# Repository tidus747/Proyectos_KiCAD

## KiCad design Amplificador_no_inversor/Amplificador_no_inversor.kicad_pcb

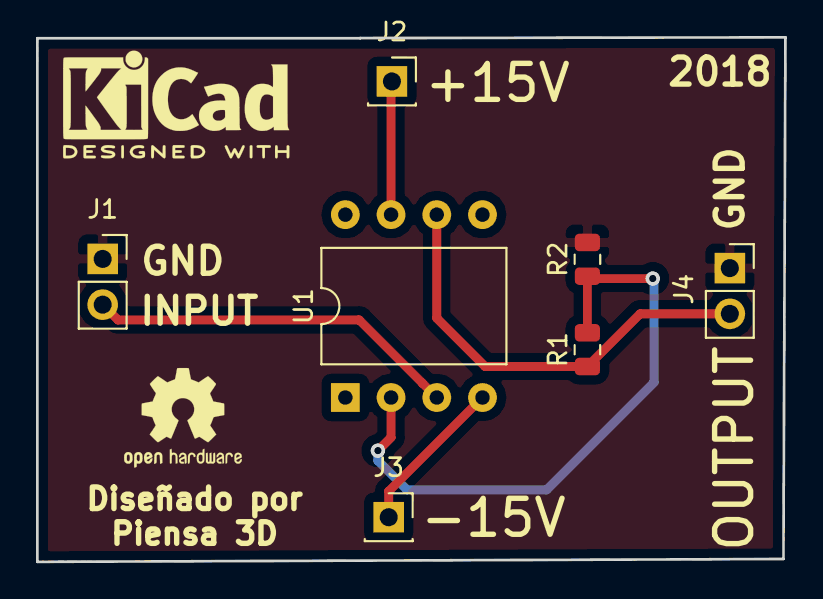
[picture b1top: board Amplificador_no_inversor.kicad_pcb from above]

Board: 2 copper layers, 41.6 x 29.1 mm, 7 parts (0 on the bottom side), 6 nets.

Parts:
J1, J4: Conn_01x02_Male; PinSocket_1x02_P2.54mm_Vertical
J2, J3: Conn_01x01_Male; PinSocket_1x01_P2.54mm_Vertical
R1, R2: 1k; R_0805_2012Metric
U1: LM741; DIP-8_W10.16mm

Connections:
+15V: J2.1, U1.7
-15V: J3.1, U1.4
GND: J1.1, J4.1, R2.2
unnamed: J1.2, U1.3
unnamed: J4.2, R1.1, U1.6
unnamed: R1.2, R2.1, U1.2

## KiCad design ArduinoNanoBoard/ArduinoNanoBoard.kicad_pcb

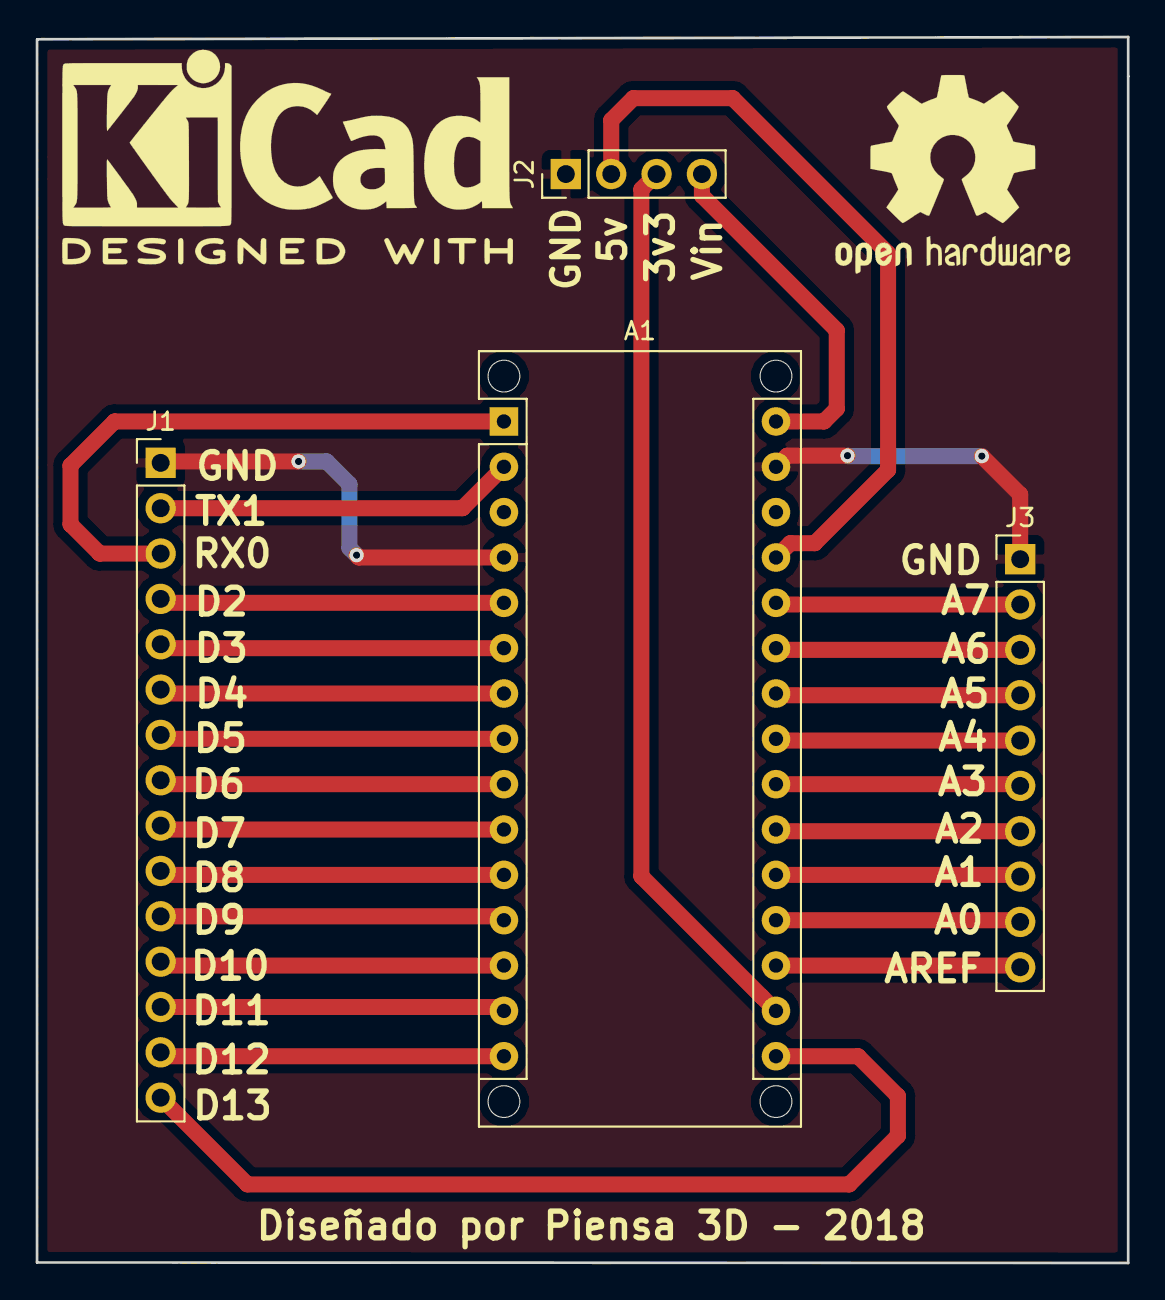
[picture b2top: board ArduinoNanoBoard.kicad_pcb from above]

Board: 2 copper layers, 61.1 x 68.7 mm, 4 parts (0 on the bottom side), 27 nets.

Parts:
A1: Arduino_Nano_v3.x; Arduino_Nano_WithMountingHoles
J1: Conn_01x15_Male; PinHeader_1x15_P2.54mm_Vertical
J2: Conn_01x04_Male; PinHeader_1x04_P2.54mm_Vertical
J3: Conn_01x10_Male; PinHeader_1x10_P2.54mm_Vertical

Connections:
GND: A1.4, A1.29, J1.1, J2.1, J3.1
unnamed: A1.1, J1.3
unnamed: A1.2, J1.2
unnamed: A1.5, J1.4
unnamed: A1.6, J1.5
unnamed: A1.7, J1.6
unnamed: A1.8, J1.7
unnamed: A1.9, J1.8
unnamed: A1.10, J1.9
unnamed: A1.11, J1.10
unnamed: A1.12, J1.11
unnamed: A1.13, J1.12
unnamed: A1.14, J1.13
unnamed: A1.15, J1.14
unnamed: A1.16, J1.15
unnamed: A1.17, J2.3
unnamed: A1.18, J3.10
unnamed: A1.19, J3.9
unnamed: A1.20, J3.8
unnamed: A1.21, J3.7
unnamed: A1.22, J3.6
unnamed: A1.23, J3.5
unnamed: A1.24, J3.4
unnamed: A1.25, J3.3
unnamed: A1.26, J3.2
unnamed: A1.27, J2.2
unnamed: A1.30, J2.4

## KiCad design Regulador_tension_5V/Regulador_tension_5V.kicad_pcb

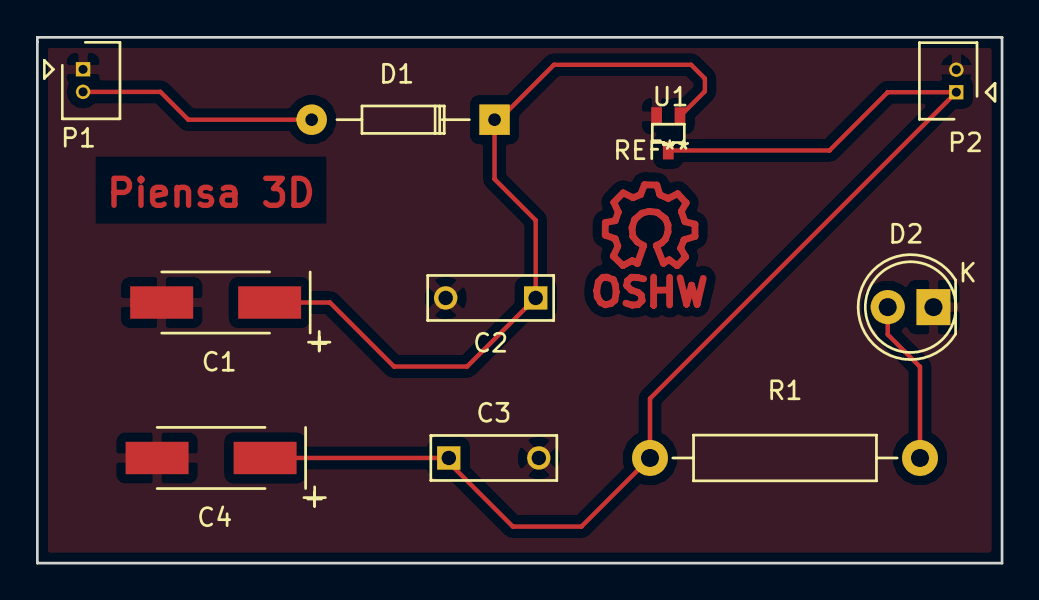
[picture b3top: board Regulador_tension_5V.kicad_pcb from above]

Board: 2 copper layers, 53.6 x 29.2 mm, 10 parts (0 on the bottom side), 5 nets.

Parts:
C1: 10uF; TantalC_SizeC_EIA-6032_HandSoldering
C2, C3: 100nF; C_Rect_L7_W2.5_P5
C4: 220uF; TantalC_SizeC_EIA-6032_HandSoldering
D1: 1N4001; Diode_DO-35_SOD27_Horizontal_RM10
D2: LED; LED-5MM
P1, P2: CONN_01X02; Connector_Molex_PicoBlade_53047-0210
R1: 1k; Resistor_Horizontal_RM15mm
U1: LM7805; SOT-323

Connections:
GND: C1.2, C2.2, C3.2, C4.2, D2.1, P1.1, P2.2, U1.2
unnamed: C1.1, C2.1, D1.1, U1.1
unnamed: C3.1, C4.1, P2.1, R1.1, U1.3
unnamed: D1.2, P1.2
unnamed: D2.2, R1.2

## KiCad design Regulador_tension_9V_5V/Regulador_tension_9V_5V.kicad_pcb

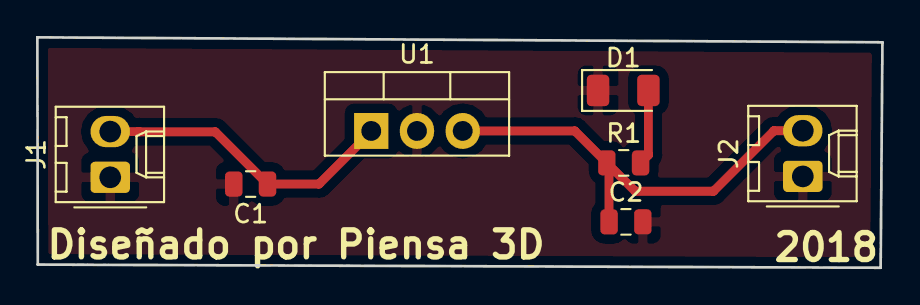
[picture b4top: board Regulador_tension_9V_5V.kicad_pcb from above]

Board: 2 copper layers, 46.9 x 12.8 mm, 7 parts (0 on the bottom side), 4 nets.

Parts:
C1: 0,33uF; C_0805_2012Metric
C2: 0,1uF; C_0805_2012Metric
D1: LED; LED_1206_3216Metric
J1, J2: Conn_01x02_Male; Molex_KK-254_AE-6410-02A_1x02_P2.54mm_Vertical
R1: 1K; R_0805_2012Metric
U1: L7805; TO-220-3_Vertical

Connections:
GND: C1.2, C2.2, D1.1, J1.1, J2.1, U1.2
unnamed: C1.1, J1.2, U1.1
unnamed: C2.1, J2.2, R1.1, U1.3
unnamed: D1.2, R1.2
